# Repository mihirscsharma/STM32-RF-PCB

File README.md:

# STM32-RF-PCB
STM32 based radio-frequency transceiver PCB for IoT applications on KiCad:

This project is a fully custom 2-layer PCB designed around the STM32L432 microcontroller and the NRF24L01+ RF transceiver. Built using KiCad 7, it features USB power/data, an SWD debug interface, and an impedance-matched antenna section.
---

---
## Features

- **MCU**: STM32L432K (32-bit ARM Cortex-M4)
- **RF**: NRF24L01+ 2.4 GHz transceiver
- **Power**: USB 5V input, onboard 3.3V regulation
- **Interface**:
  - SWD header for debugging/programming
  - USB interface for data/power
- **RF Matching Network** for antenna output
- **SMD-Only Design** for compact assembly
- **4-Layer PCB**

---

## Design Tools & Stack

- **KiCad 7**
  - Schematic capture
  - PCB layout
  - 3D visualization
  - DRC/ERC validation
- **ST-Link v2** for programming/debugging

---

## What I Learned

- Net class management, trace width/spacing tuning  
- RF layout constraints (short matched lines, clean ground returns, Differential pairing)  
- SWD routing and antenna network integration  
- 3D verification and design-for-manufacturability (DFM)

---

## Repo Contents

| Folder / File           | Description                               |
|-------------------------|-------------------------------------------|
| `pcb.kicad_sch          | KiCad schematic           |
| `pcb.kicad_pcb          | KiCad layout              |

## Next Steps

- Assemble and test the board
- Flash custom STM32 firmware
- Implement RF comm layer (transmit/receive)
- Explore sensor integration over SPI/UART/I2C

## Contact

Feel free to reach out or connect if you're working on RF or PCB hardware!

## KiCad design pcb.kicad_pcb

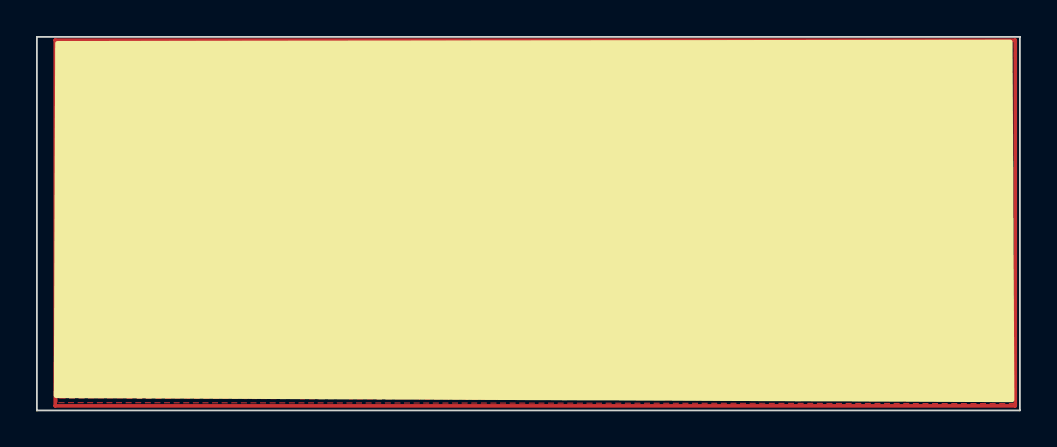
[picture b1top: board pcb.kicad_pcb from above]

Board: 4 copper layers, 54.6 x 20.8 mm, 36 parts (0 on the bottom side), 30 nets.

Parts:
C1, C3, C6: 10u; C_0402_1005Metric
C2: 33n; C_0402_1005Metric
C4, C5, C7: 10n; C_0402_1005Metric
C8, C10: 12p; C_0402_1005Metric
C9: 2n2; C_0402_1005Metric
C11: 4p7; C_0402_1005Metric
C12: 1p5; C_0402_1005Metric
C13: 1p; C_0402_1005Metric
C14: 1u; C_0402_1005Metric
C15, C16, C17, C18: 100n; C_0402_1005Metric
D1, D2: LED; LED_0603_1608Metric
F1: 100mA; Fuse_1206_3216Metric
FB1: 100 @ 100MHz; L_0805_2012Metric
J3: Conn_ARM_JTAG_SWD_10; PinHeader_2x05_P1.27mm_Vertical_SMD
L1: 8n2; L_0402_1005Metric
L2: 3n9; L_0402_1005Metric
L3: 2n7; L_0402_1005Metric
R1: 22k; R_0603_1608Metric
R2: 1M; R_0603_1608Metric
R3: 10k; R_0603_1608Metric
R4, R5: 2k2; R_0603_1608Metric
U1: nRF24L01P; QFN-20-1EP_4x4mm_P0.5mm_EP2.5x2.5mm
U2: XC6206P332MR; SOT-23
U3: USBLC6-2SC6; SOT-23-6
U4: STM32L432KBUx; QFN-32-1EP_5x5mm_P0.5mm_EP3.45x3.45mm
Y1: Crystal_GND24; Crystal_SMD_3225-4Pin_3.2x2.5mm

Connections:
+3V3: C1.1, C4.1, C5.1, C6.1, C7.1, C14.1, C15.1, C16.1, C17.1, J3.1 (VTref), R1.1, U1.7 (VDD), U1.15 (VDD), U1.18 (VDD), U2.2 (VO), U4.1 (VDD), U4.5 (VDDA), U4.17 (VDD)
+5V: F1.2, U3.5 (VBUS)
GND: C1.2, C2.2, C3.2, C4.2, C5.2, C6.2, C7.2, C8.2, C9.1, C10.2, C11.1, C13.1, C14.2, C15.2, C16.2, C17.2, C18.2, J3.3 (GND), J3.5 (GND), J3.9 (GNDDetect), R3.2, R4.2, R5.2, U1.8 (VSS), U1.14 (VSS), U1.17 (VSS), U1.20 (VSS), U2.1 (GND), U3.2 (GND), U4.16 (VSS), U4.32 (VSS), U4.33 (VSS), Y1.2, Y1.4
NRF_ANT1: L1.1, L3.2, U1.12 (ANT1)
NRF_ANT2: L1.2, L2.1, U1.13 (ANT2)
NRF_CE: U1.1 (CE), U4.30 (PB7)
NRF_IRQ: U1.6 (IRQ), U4.25 (PA15)
NRF_VDD_PA: C9.2, C11.2, L3.1, U1.11 (VDD_PA)
NRF_XC1: C8.1, R2.1, U1.10 (XC1), Y1.1
NRF_XC2: C10.1, R2.2, U1.9 (XC2), Y1.3
NRST: C18.1, J3.10 (~RESET)
unnamed: C2.1, U1.19 (DVDD)
unnamed: C12.1, L2.2
unnamed: C12.2, C13.2
unnamed: D1.1 (K), R4.1
unnamed: D1.2 (A), U4.9 (PA3)
unnamed: D2.1 (K), R5.1
unnamed: D2.2 (A), U4.8 (PA2)
unnamed: F1.1, FB1.1
unnamed: C3.1, FB1.2, U2.3 (VI)
unnamed: R1.2, U1.16 (IREF)
unnamed: R3.1, U4.31 (PH3)
SPI3_!CS: U1.2 (CSN), U4.29 (PB6)
SPI3_MISO: U1.5 (MISO), U4.27 (PB4)
SPI3_MOSI: U1.4 (MOSI), U4.28 (PB5)
SPI3_SCK: U1.3 (SCK), U4.26 (PB3)
SWCLK: J3.4 (SWDCLK/TCK), U4.24 (PA14)
SWDIO: J3.2 (SWDIO/TMS), U4.23 (PA13)
USB_D+: U3.1 (I/O1), U4.22 (PA12)
USB_D-: U3.3 (I/O2), U4.21 (PA11)

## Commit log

2025-07-03 Update LICENSE
